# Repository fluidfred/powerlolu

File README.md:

powerlolu
=========

High Power Pololu Board (Powerlolu) based on A4989 - can be connected to RAMPS Pololu port

Description
------------

Powerlolu can drive stepper motors up to 500 Watts, drawing currents up to 10 Amps. 
The existing Pololu boards found in common RepRap 3D printers are at their limits when 
driving the 2 Nema17 z-axis stepper motors in parallel. 

Continuous z-axis movement can cause the board to overheat. These boards hardly drive 
stepper motors bigger than a Nema17. To avoid overheating or to drive larger motors a 
more powerful driver board is needed.

The Powerlolu board enables the use of bigger stepper motors for a wide range of uses. 
This could be the conversion of manual milling machines into computer controlled milling 
machines (CNC-Machines) using the affordable electronics such as Arduino and RAMPS. 
Building 3D printers with a larger print volume or with larger extruders would be possible.

Tested the design by connecting a Nema43 stepper motor by Nanotec Electronic (capable of 
6.6 Amps per coil, Torque 2000Ncm, Weight 8,4kg) to a Powerlolu attached to a 3D printer's 
RAMPS X-port.

A short video of the new driver can be seen on YouTube at
https://www.youtube.com/watch?v=G9FWvhZI7rs .

After two hours of motor usage the Powerlolu board only got luke warm - however see Installation Note

The schematics for the Powerlolu driver are freely available at https://github.com/fluidfred/powerlolu.

Technical specifications:

* 3-wire control with DIR, STEP, Enable-signal, compatible to the Pololu board
* Supply voltage of the stepper motor from 12V to 50V
* Adjustable stepping via SMD-jumper, 1, 1/2, 1/4, 1/16 (default) steps
* Precision pot to adjust the current limiter
* no extra heat sink required due to passive cooling up to NEMA 23 stepper motors.
* Molex snap-on connector for connecting the RAMPS board to the Powerlolu
* Dimensions PCB: 75.5mm x 65mm

Important installation note:
----------------------------
Observe the heat emission when using stepper motors larger than NEMA 23. 
If necessary, implement a cooling system, i.e. heat sinks mounted at the power-Mosfets and a fan. 
Each individual Powerlolu should be protected by connecting an appropriate fuse between VBB (X2) 
and the power source of the stepper motor.

More installation notes can be found under http://wiki.germanreprap.com/en/handbuch/powerlolu concerning wiring with RAMPS and current limiter adjustment.

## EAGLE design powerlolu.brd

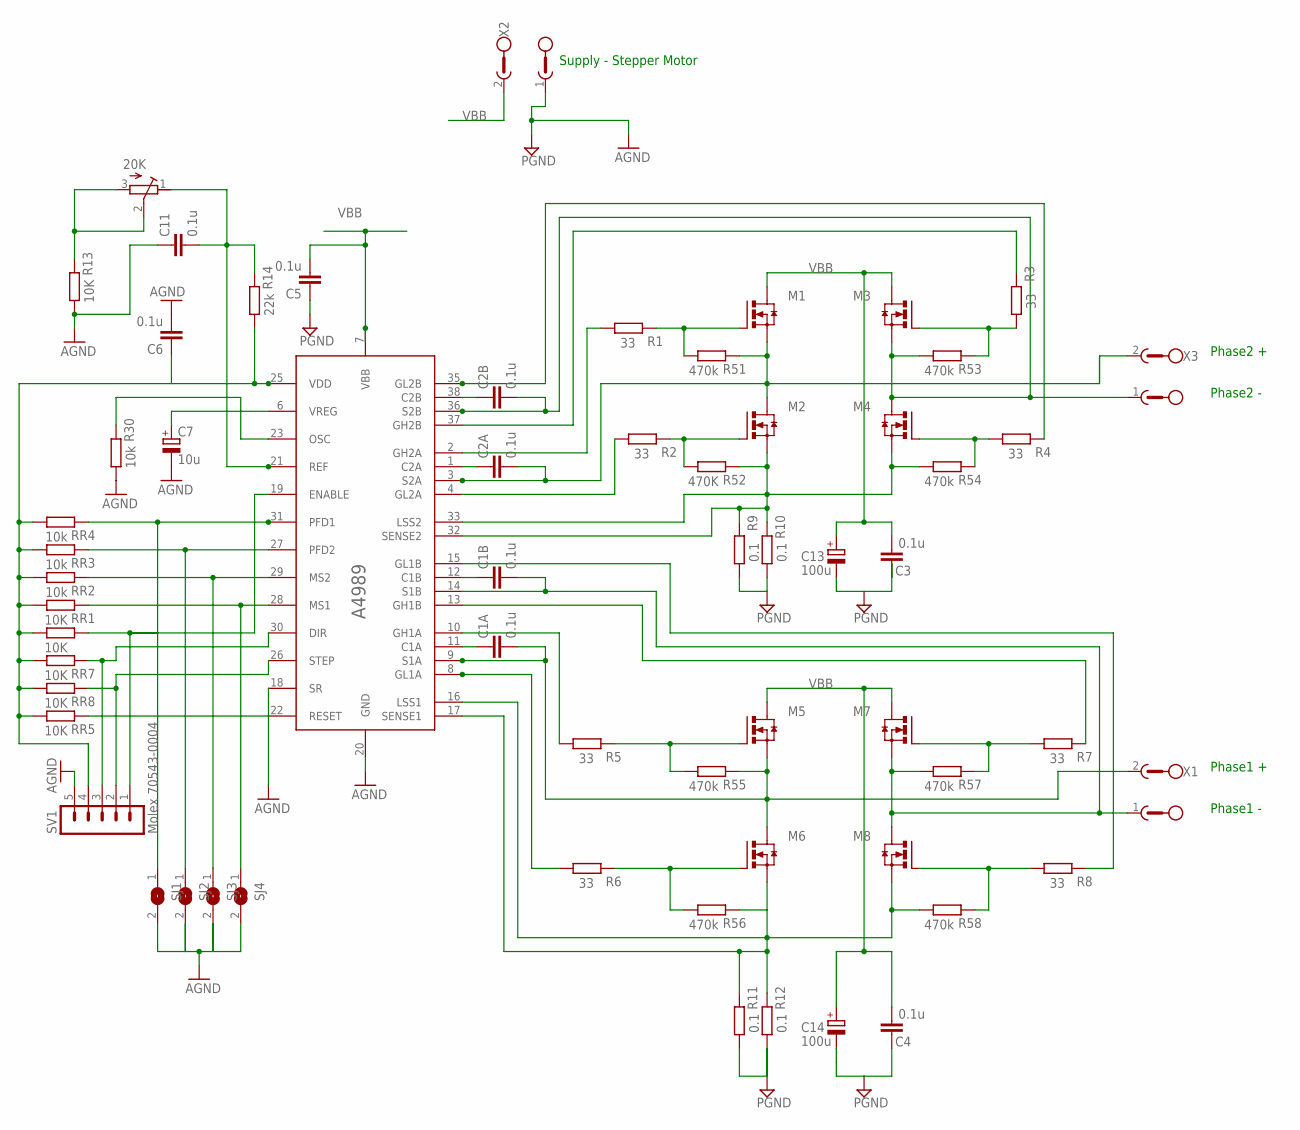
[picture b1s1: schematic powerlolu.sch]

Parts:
A4989: A4989; TSSOP39
C1A, C1B, C2A, C2B, C3, C4, C5, C6, C11: 0.1u; C0603
C7: 10u; 153CLV-0605
C13, C14: 100u; E5-10,5
M1, M2, M3, M4, M5, M6, M7, M8: IRLR024N; TO252
R1, R2, R3, R4, R5, R6, R7, R8: 33; R0603
R9, R10, R11, R12: 0.1; R2512
R13: 10K; R0603
R14: 22k; R0603
R30: 10k; R0603
R51, R53, R54, R55, R56, R57, R58: 470k; R0603
R52: 470K; R0603
RR1, RR5, RR6, RR7, RR8: 10K; R0603
RR2, RR3, RR4: 10k; R0603
SJ1, SJ2, SJ3, SJ4: SJ
SV1: Molex 70543-0004; MA05-1
U$1: 20K; BOURNS_3266W
X1, X2, X3: GMGDS32; GMKDS32

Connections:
GND: A4989.18 (SR), A4989.20 (GND), C3.1, C4.1, C5.1, C6.2, C7.-, C11.1, C13.-, C14.-, R9.2, R10.2, R11.2, R12.2, R13.2, R30.2, SJ1.2, SJ2.2, SJ3.2, SJ4.2, SV1.5, X2.1; also elsewhere on the board
unnamed: A4989.27 (PFD2), RR3.1, SJ2.1
unnamed: A4989.29 (MS2), RR2.1, SJ3.1
unnamed: A4989.28 (MS1), RR1.1, SJ4.1
unnamed: M2.1 (G), R2.1, R52.2
unnamed: M1.1 (G), R1.1, R51.2
unnamed: M3.1 (G), R3.2, R53.1
unnamed: M4.1 (G), R4.2, R54.1
unnamed: M6.1 (G), R6.1, R56.2
unnamed: M5.1 (G), R5.1, R55.2
unnamed: M7.1 (G), R7.2, R57.1
unnamed: M8.1 (G), R8.2, R58.1
unnamed: A4989.23 (OSC), R30.1
unnamed: R13.1, U$1.2 (S), U$1.3 (E)
unnamed: A4989.22 (RESET), RR5.1
unnamed: A4989.21 (REF), C11.2, R14.1, U$1.1 (A)
unnamed: A4989.37 (GH2B), R3.1
unnamed: A4989.2 (GH2A), R1.2
unnamed: A4989.35 (GL2B), R4.1
unnamed: A4989.4 (GL2A), R2.2
unnamed 21: A4989.26 (STEP), RR8.1, SV1.2; also elsewhere on the board
unnamed: A4989.32 (SENSE2), A4989.33 (LSS2), M2.2 (S), M4.2 (S), R9.1, R10.1, R52.1, R54.2
unnamed 23: A4989.19 (ENABLE), RR6.1, SV1.1; also elsewhere on the board
unnamed: A4989.10 (GH1A), R5.2
unnamed: A4989.13 (GH1B), R7.1
unnamed: A4989.15 (GL1B), R8.1
unnamed: A4989.8 (GL1A), R6.2
unnamed: A4989.12 (C1B), C1B.1
unnamed: A4989.16 (LSS1), A4989.17 (SENSE1), M6.2 (S), M8.2 (S), R11.1, R12.1, R56.1, R58.2
unnamed: A4989.31 (PFD1), RR4.1, SJ1.1
unnamed: A4989.11 (C1A), C1A.1
unnamed: A4989.1 (C2A), C2A.1
unnamed: A4989.38 (C2B), C2B.1
unnamed 34: A4989.30 (DIR), RR7.1, SV1.3; also elsewhere on the board
unnamed 35: A4989.25 (VDD), C6.1, R14.2, RR1.2, RR2.2, RR3.2, RR4.2, RR5.2, RR6.2, RR7.2, RR8.2, SV1.4; also elsewhere on the board
unnamed: A4989.6 (VREG), C7.+
P1+: A4989.9 (S1A), C1A.2, M5.2 (S), M6.3 (D), R55.1, X1.2
P1-: A4989.14 (S1B), C1B.2, M7.2 (S), M8.3 (D), R57.2, X1.1
P2+: A4989.3 (S2A), C2A.2, M1.2 (S), M2.3 (D), R51.1, X3.2
P2-: A4989.36 (S2B), C2B.2, M3.2 (S), M4.3 (D), R53.2, X3.1
VBB: A4989.7 (VBB), C3.2, C4.2, C5.2, C13.+, C14.+, M1.3 (D), M3.3 (D), M5.3 (D), M7.3 (D), X2.2

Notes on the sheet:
Supply - Stepper Motor
Phase2 +
Phase2 -
Phase1 +
Phase1 -

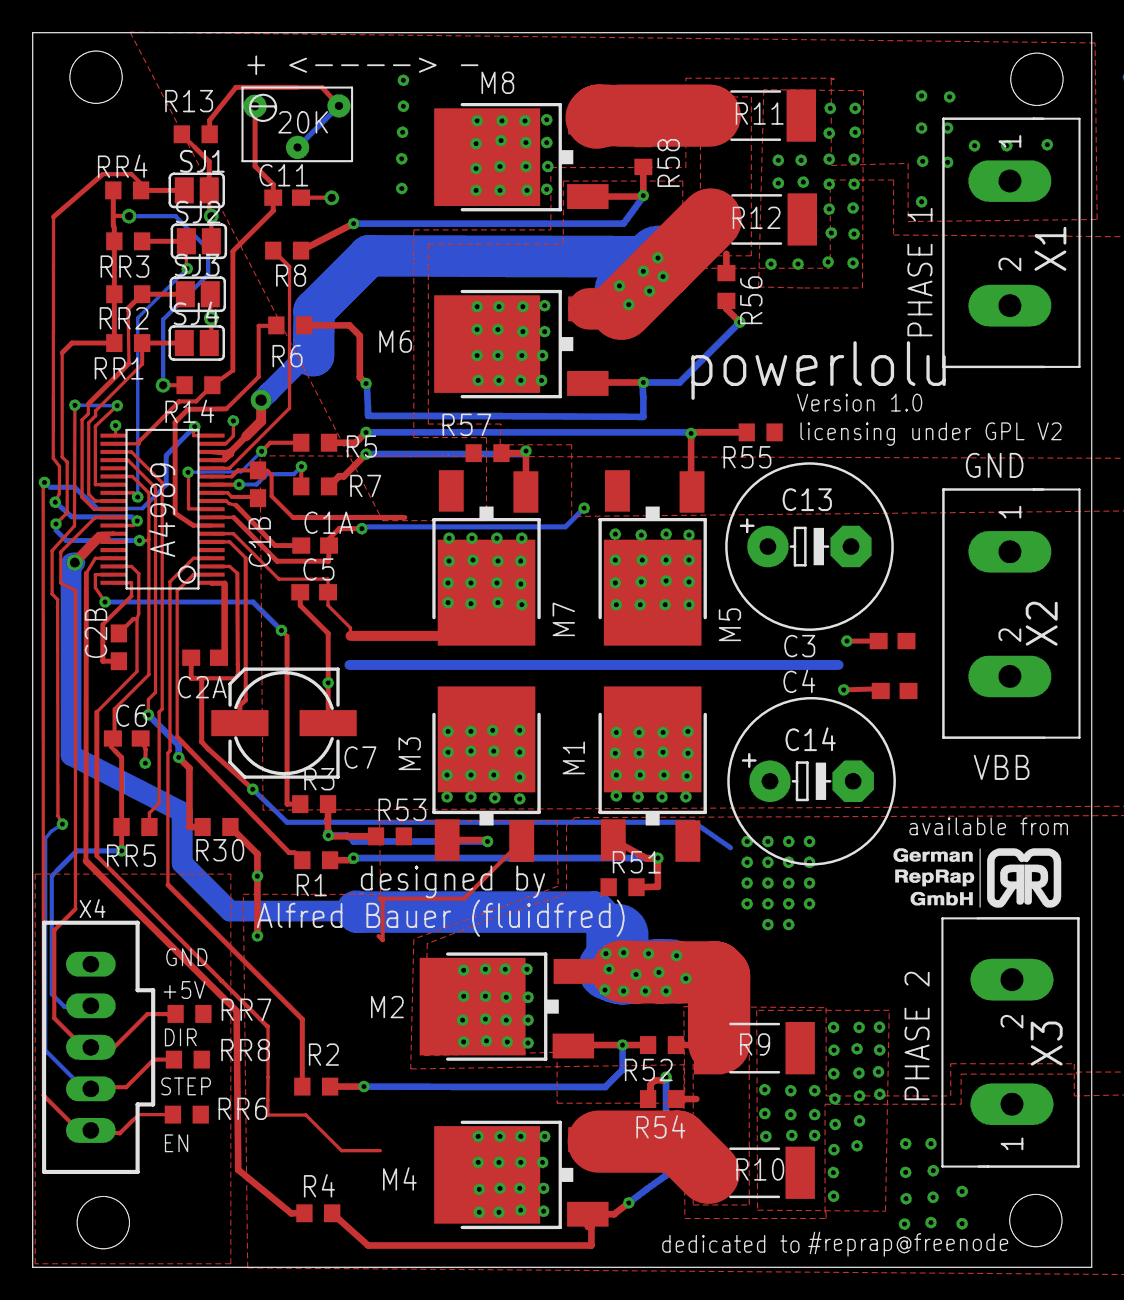
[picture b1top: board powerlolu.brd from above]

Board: 2 copper layers, 64.8 x 75.5 mm, 61 parts (0 on the bottom side), 41 nets.

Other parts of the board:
X4: C-GRID-05-70543; 70543-05

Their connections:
GND: X4.5; also elsewhere on the board
unnamed 21: X4.2; also elsewhere on the board
unnamed 23: X4.1; also elsewhere on the board
unnamed 34: X4.3; also elsewhere on the board
unnamed 35: X4.4; also elsewhere on the board

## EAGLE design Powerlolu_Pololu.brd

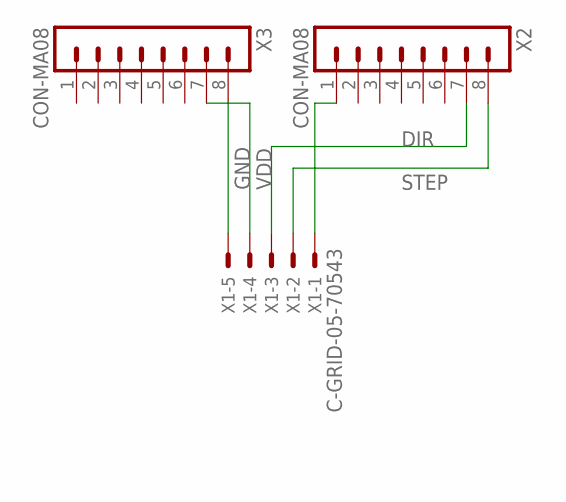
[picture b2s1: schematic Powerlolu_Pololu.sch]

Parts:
X1: C-GRID-05-70543; 70543-05
X2, X3: CON-MA08; MA08

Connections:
DIR: X1.3, X2.7
GND: X1.5, X3.8
unnamed: X1.1, X2.1
STEP: X1.2, X2.8
VDD: X1.4, X3.7

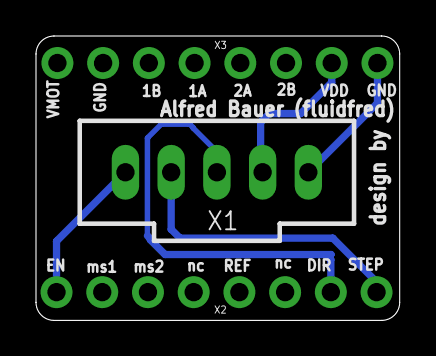
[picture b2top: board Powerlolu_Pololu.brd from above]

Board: 2 copper layers, 20.2 x 15.8 mm, 3 parts (0 on the bottom side), 5 nets.

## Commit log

2012-12-18 First Version
2012-12-18 V1.1
2012-12-19 cosmetic changes

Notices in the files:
powerlolu.brd:
licensing under GPL V2
